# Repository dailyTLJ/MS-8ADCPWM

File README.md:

# MS_8ADCPWM

Board with 2x ADS8688a chips (8 analog inputs each) and 1x TLC5947 chip (24ch LED PWM driver).

Issues when chaining more than 4 boards (8 ADS8688a ics)

## next iteration

* digital buffers, to allow larger chains
* default-off on LED channels, in the absence of control signal 
* power-in with screw terminals?

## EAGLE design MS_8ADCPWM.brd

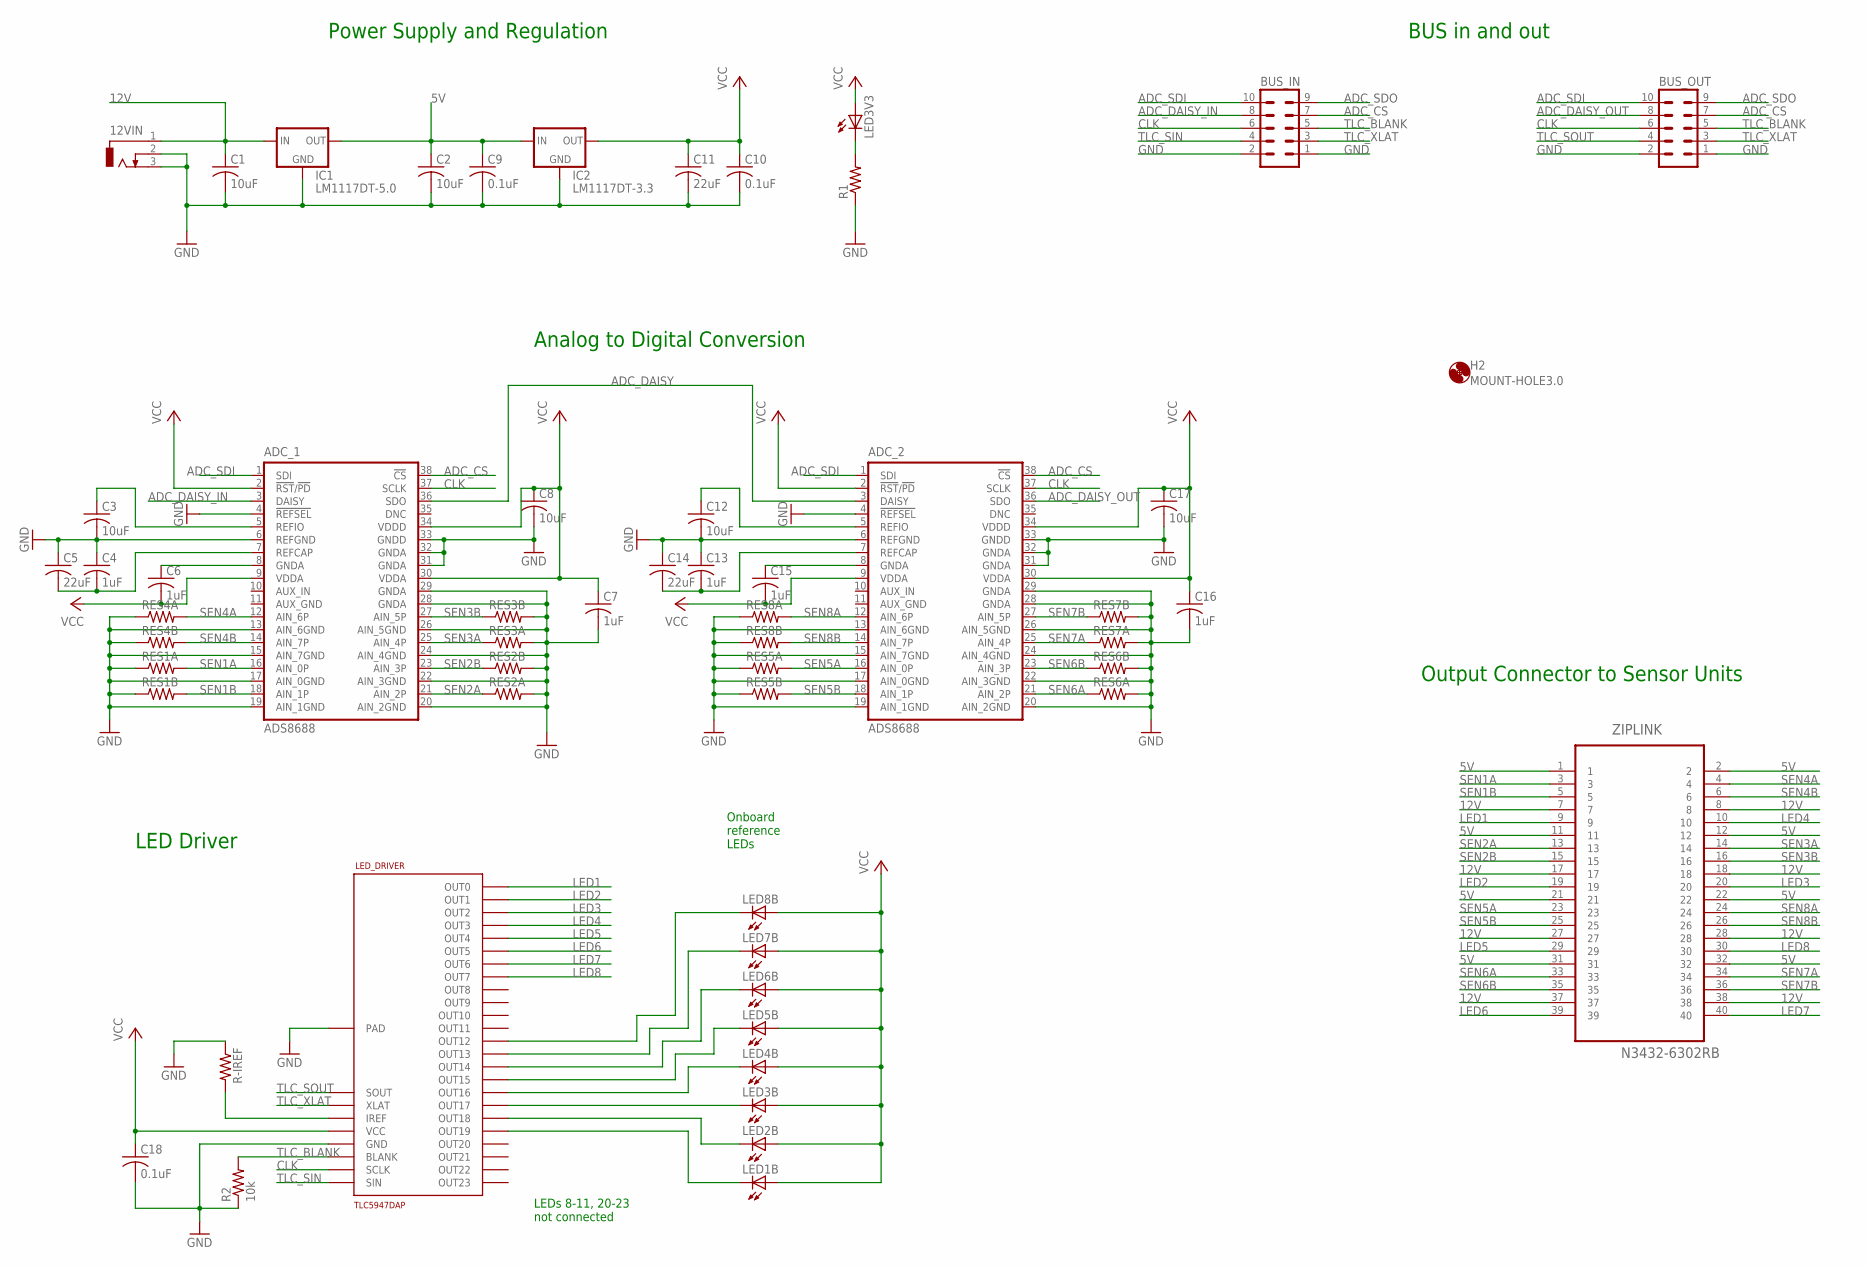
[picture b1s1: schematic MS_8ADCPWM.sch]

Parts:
12VIN: DCJ0303
ADC_1, ADC_2: ADS8688; DBT_R-PDSO-G38
BUS_IN: ML10
BUS_OUT: ML10
C1, C2, C3, C8, C12, C17: 10uF; C0805
C4, C6, C7, C13, C15, C16: 1uF; C0805
C5, C11, C14: 22uF; C0805
C9, C10, C18: 0.1uF; C0805
H2: MOUNT-HOLE3.0; 3,0
IC1: LM1117DT-5.0; TO252
IC2: LM1117DT-3.3; TO252
LED1B, LED2B, LED3B, LED4B, LED5B, LED6B, LED7B, LED8B: LEDSMD2PLCC; 2-PLCC
LED3V3: LEDCHIPLED_0805; CHIPLED_0805
LED_DRIVER: TLC5947DAP; HTSSOP32DAP
R1: R-US_R0805; R0805
R2: 10k; R1206
R-IREF: R-US_R1206; R1206
RES1A, RES1B, RES2A, RES2B, RES3A, RES3B, RES4A, RES4B, RES5A, RES5B, RES6A, RES6B, RES7A, RES7B, RES8A, RES8B: R-US_R1206; R1206
ZIPLINK: N3432-6302RB; 3M_N3432-6302RB

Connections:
5V: C2.1, C9.1, IC1.3 (OUT), IC2.2 (IN), ZIPLINK.1, ZIPLINK.2, ZIPLINK.11, ZIPLINK.12, ZIPLINK.21, ZIPLINK.22, ZIPLINK.31, ZIPLINK.32
12V: 12VIN.1, C1.1, IC1.2 (IN), ZIPLINK.7, ZIPLINK.8, ZIPLINK.17, ZIPLINK.18, ZIPLINK.27, ZIPLINK.28, ZIPLINK.37, ZIPLINK.38
ADC_CS: ADC_1.38 (!CS), ADC_2.38 (!CS), BUS_IN.7, BUS_OUT.7
ADC_DAISY: ADC_1.36 (SDO), ADC_2.3 (DAISY)
ADC_DAISY_IN: ADC_1.3 (DAISY), BUS_IN.8
ADC_DAISY_OUT: ADC_2.36 (SDO), BUS_OUT.8
ADC_SDI: ADC_1.1 (SDI), ADC_2.1 (SDI), BUS_IN.10, BUS_OUT.10
ADC_SDO: BUS_IN.9, BUS_OUT.9
CLK: ADC_1.37 (SCLK), ADC_2.37 (SCLK), BUS_IN.6, BUS_OUT.6, LED_DRIVER.3 (SCLK)
GND: 12VIN.2, 12VIN.3, ADC_1.4 (!REFSEL), ADC_1.6 (REFGND), ADC_1.13 (AIN_6GND), ADC_1.15 (AIN_7GND), ADC_1.17 (AIN_0GND), ADC_1.19 (AIN_1GND), ADC_1.20 (AIN_2GND), ADC_1.22 (AIN_3GND), ADC_1.24 (AIN_4GND), ADC_1.26 (AIN_5GND), ADC_1.28 (GNDA), ADC_1.29 (GNDA), ADC_1.31 (GNDA), ADC_1.32 (GNDA), ADC_1.33 (GNDD), ADC_2.4 (!REFSEL), ADC_2.6 (REFGND), ADC_2.13 (AIN_6GND), ADC_2.15 (AIN_7GND), ADC_2.17 (AIN_0GND), ADC_2.19 (AIN_1GND), ADC_2.20 (AIN_2GND), ADC_2.22 (AIN_3GND), ADC_2.24 (AIN_4GND), ADC_2.26 (AIN_5GND), ADC_2.28 (GNDA), ADC_2.29 (GNDA), ADC_2.31 (GNDA), ADC_2.32 (GNDA), ADC_2.33 (GNDD), BUS_IN.1, BUS_IN.2, BUS_OUT.1, BUS_OUT.2, C1.2, C2.2, C3.2, C4.1, C5.1, C7.2, C8.2, C9.2, C10.2, C11.2, C12.2, C13.1, C14.1, C16.2, C17.2, C18.2, IC1.1 (GND), IC2.1 (GND), LED_DRIVER.1 (GND), LED_DRIVER.EXP (PAD), R1.1, R2.1, R-IREF.1, RES1A.1, RES1B.1, RES2A.2, RES2B.2, RES3A.2, RES3B.2, RES4A.1, RES4B.1, RES5A.1, RES5B.1, RES6A.2, RES6B.2, RES7A.2, RES7B.2, RES8A.1, RES8B.1
LED1: LED_DRIVER.5 (OUT0), ZIPLINK.9
LED2: LED_DRIVER.6 (OUT1), ZIPLINK.19
LED3: LED_DRIVER.7 (OUT2), ZIPLINK.20
LED4: LED_DRIVER.8 (OUT3), ZIPLINK.10
LED5: LED_DRIVER.9 (OUT4), ZIPLINK.29
LED6: LED_DRIVER.10 (OUT5), ZIPLINK.39
LED7: LED_DRIVER.11 (OUT6), ZIPLINK.40
LED8: LED_DRIVER.12 (OUT7), ZIPLINK.30
unnamed: ADC_1.5 (REFIO), C3.1
unnamed: LED3V3.C, R1.2
unnamed: ADC_2.7 (REFCAP), C13.2, C14.2
unnamed: ADC_1.7 (REFCAP), C4.2, C5.2
unnamed: ADC_2.5 (REFIO), C12.1
unnamed: ADC_2.8 (GNDA), C15.1
unnamed: ADC_1.8 (GNDA), C6.1
unnamed: LED1B.C, LED_DRIVER.24 (OUT19)
unnamed: LED_DRIVER.31 (IREF), R-IREF.2
unnamed: LED2B.C, LED_DRIVER.23 (OUT18)
unnamed: LED3B.C, LED_DRIVER.22 (OUT17)
unnamed: LED4B.C, LED_DRIVER.21 (OUT16)
unnamed: LED5B.C, LED_DRIVER.20 (OUT15)
unnamed: LED6B.C, LED_DRIVER.19 (OUT14)
unnamed: LED7B.C, LED_DRIVER.18 (OUT13)
unnamed: LED8B.C, LED_DRIVER.17 (OUT12)
SEN1A: ADC_1.16 (AIN_0P), RES1A.2, ZIPLINK.3
SEN1B: ADC_1.18 (AIN_1P), RES1B.2, ZIPLINK.5
SEN2A: ADC_1.21 (AIN_2P), RES2A.1, ZIPLINK.13
SEN2B: ADC_1.23 (AIN_3P), RES2B.1, ZIPLINK.15
SEN3A: ADC_1.25 (AIN_4P), RES3A.1, ZIPLINK.14
SEN3B: ADC_1.27 (AIN_5P), RES3B.1, ZIPLINK.16
SEN4A: ADC_1.12 (AIN_6P), RES4A.2, ZIPLINK.4
SEN4B: ADC_1.14 (AIN_7P), RES4B.2, ZIPLINK.6
SEN5A: ADC_2.16 (AIN_0P), RES5A.2, ZIPLINK.23
SEN5B: ADC_2.18 (AIN_1P), RES5B.2, ZIPLINK.25
SEN6A: ADC_2.21 (AIN_2P), RES6A.1, ZIPLINK.33
SEN6B: ADC_2.23 (AIN_3P), RES6B.1, ZIPLINK.35
SEN7A: ADC_2.25 (AIN_4P), RES7A.1, ZIPLINK.34
SEN7B: ADC_2.27 (AIN_5P), RES7B.1, ZIPLINK.36
SEN8A: ADC_2.12 (AIN_6P), RES8A.2, ZIPLINK.24
SEN8B: ADC_2.14 (AIN_7P), RES8B.2, ZIPLINK.26
TLC_BLANK: BUS_IN.5, BUS_OUT.5, LED_DRIVER.2 (BLANK), R2.2
TLC_SIN: BUS_IN.4, LED_DRIVER.4 (SIN)
TLC_SOUT: BUS_OUT.4, LED_DRIVER.29 (SOUT)
TLC_XLAT: BUS_IN.3, BUS_OUT.3, LED_DRIVER.30 (XLAT)
VCC: ADC_1.2 (!RST!/!PD), ADC_1.9 (VDDA), ADC_1.30 (VDDA), ADC_1.34 (VDDD), ADC_2.2 (!RST!/!PD), ADC_2.9 (VDDA), ADC_2.30 (VDDA), ADC_2.34 (VDDD), C6.2, C7.1, C8.1, C10.1, C11.1, C15.2, C16.1, C17.1, C18.1, IC2.3 (OUT), LED1B.A, LED2B.A, LED3B.A, LED3V3.A, LED4B.A, LED5B.A, LED6B.A, LED7B.A, LED8B.A, LED_DRIVER.32 (VCC)

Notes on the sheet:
Power Supply and Regulation
Analog to Digital Conversion
LED Driver
Output Connector to Sensor Units
BUS in and out
Onboard reference LEDs
LEDs 8-11, 20-23 not connected

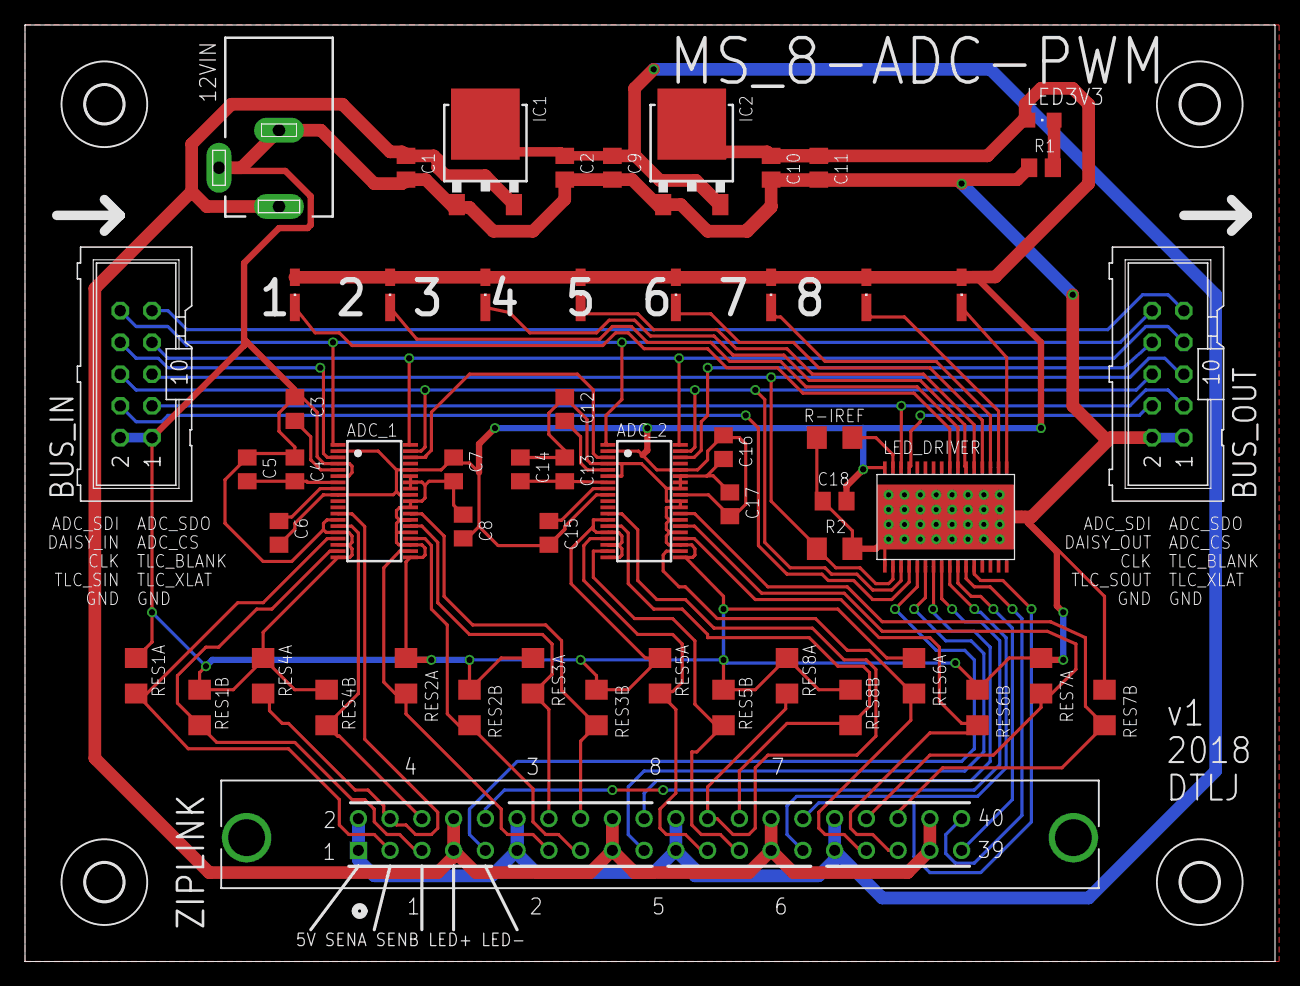
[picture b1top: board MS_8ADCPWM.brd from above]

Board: 2 copper layers, 100.0 x 74.9 mm, 59 parts (0 on the bottom side), 55 nets.

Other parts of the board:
H1, H3, H4: MOUNT-HOLE3.0; 3,0

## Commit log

2018-09-13 ready for 1st production
2018-09-13 add readme
2018-12-19 add images
